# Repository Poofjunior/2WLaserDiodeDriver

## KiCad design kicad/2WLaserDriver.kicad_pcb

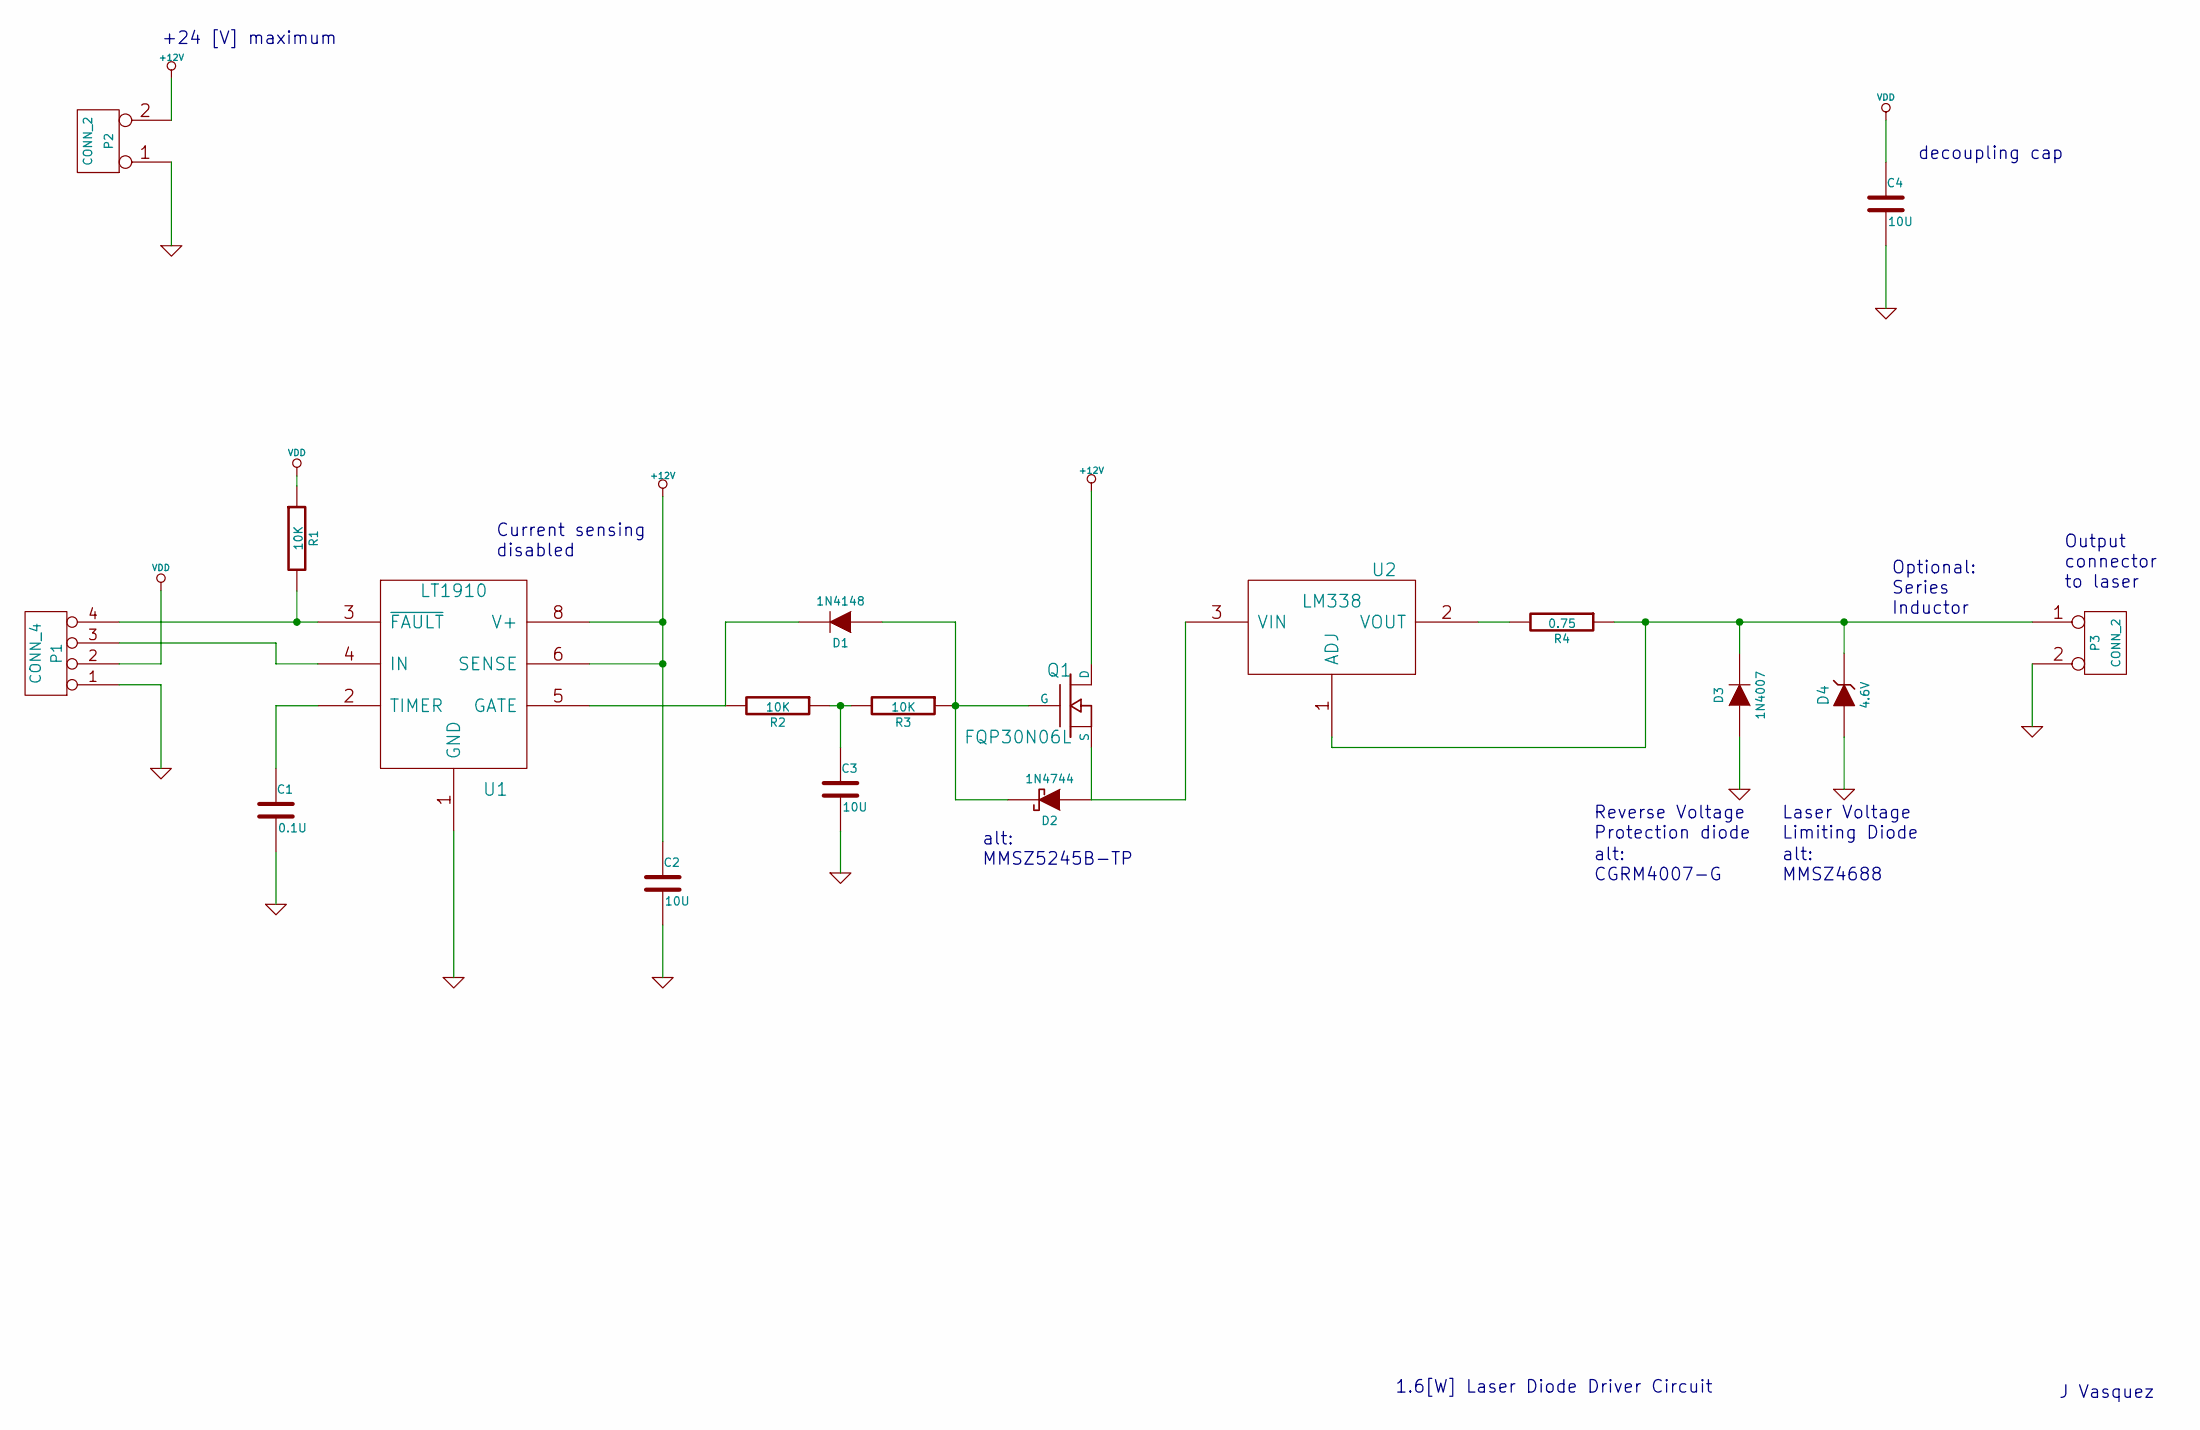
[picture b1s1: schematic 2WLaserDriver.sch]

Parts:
C1: 0.1U
C2, C3, C4: 10U
D1: 1N4148
D2: 1N4744
D3: 1N4007
D4: 4.6V
P1: CONN_4
P2, P3: CONN_2
Q1: FQP30N06L
R1, R2, R3: 10K
R4: 0.75
U1: LT1910
U2: LM338

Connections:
+12V: C2.1, P2.2 (PM), Q1.D, U1.6 (SENSE), U1.8 (V+)
GND: C1.2, C2.2, C3.2, C4.2, D3.1 (A), D4.1 (A), P1.1, P2.1, P3.2 (PM), U1.1 (GND)
unnamed: C1.1, U1.2 (TIMER)
unnamed: C3.1, R2.1, R3.2
unnamed: D1.1 (A), D2.2 (K), Q1.G, R3.1
unnamed: D1.2 (K), R2.2, U1.5 (GATE)
unnamed: D2.1 (A), Q1.S, U2.3 (VIN)
unnamed: D3.2 (K), D4.2 (K), P3.1, R4.1, U2.1 (ADJ)
unnamed: P1.3, U1.4 (IN)
unnamed: P1.4, R1.2, U1.3 (~FAULT)
unnamed: R4.2, U2.2 (VOUT)
VDD: C4.1, P1.2, R1.1

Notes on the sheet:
+24 [V] maximum
Current sensing disabled
decoupling cap
Optional: Series Inductor
1.6[W] Laser Diode Driver Circuit
Reverse Voltage Protection diode
Laser Voltage Limiting Diode
Output connector to laser
J Vasquez
alt: MMSZ5245B-TP
alt: CGRM4007-G
alt: MMSZ4688

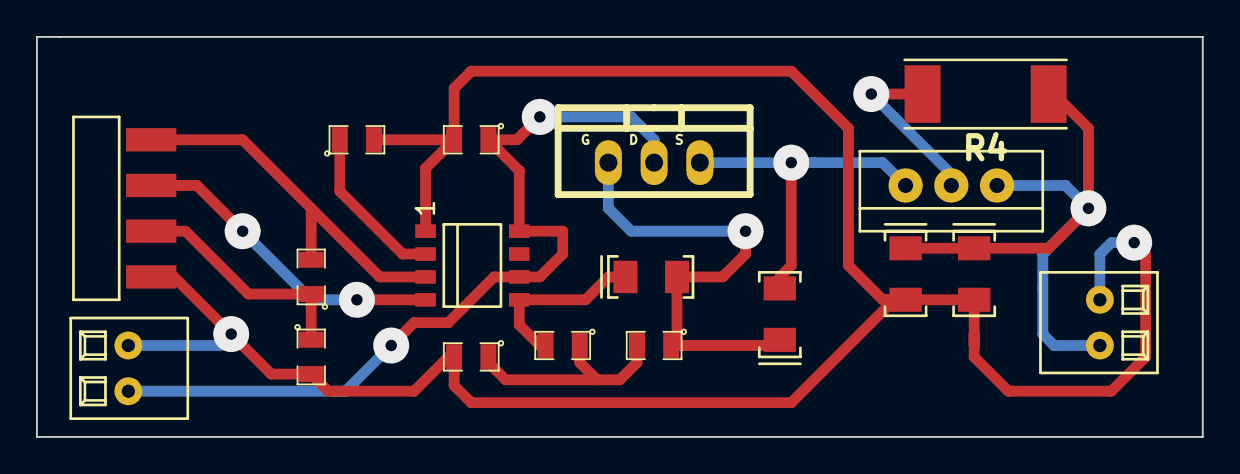
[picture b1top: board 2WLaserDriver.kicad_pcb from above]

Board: 2 copper layers, 64.8 x 22.2 mm, 18 parts (0 on the bottom side), 12 nets.

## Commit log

2014-01-12 iniial commit
2014-09-07 revised for capacitive loads
